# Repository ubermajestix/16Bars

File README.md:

# 16Bars

16Bars is a utility module designed to display how many 
measures have elapsed on a seven segment display given a clock pulse. 
The module resets every 8 or 16 measures (bars) or when the reset button is pressed.

This is my first module design and I've made several simplifying design choices:
1. A 1U version would be much more convienient
2. Reset jack would be nice to play better with midi or modules that output reset
3. Midi support? Accept MIDI TRS input for start, stop, and reset?
4. LFO output with LFO reset, could use 1st bar, n/2 bars, and last bar to self patch musical phrased LFO
## Rev 3.2 Updates and Issues

## Rev 2.0 Updates and Issues
I was successfully able to get JLCPCB to manufacture and place a lot of SMD components as I don't have the time or gear to get into surface mount, win! 

I also breadboarded out and build test PCBS to validate significant portion of the Rev 2.0 design:
- Reset button uses a transistor to send a reset signal instead of directly sending +12v when pressed
- Two transistors to normalize a wide variety of incoming clock signal voltages and send +12v pulses to trigger the three counter ICs and blink the led in the reset button 
- 8 bar reset logic confirmed, 16 bar reset logic didn't work because I was rushing to get Rev 2.0 board to production.
- Built a switch test PCB. I ordered 4 different switches and after getting incorrect footprints for the seven segment leds from Mouser I didn't trust the switch footprints. I also wanted to validate the switch weight, height, footprint size tradeoffs, validate the switches are in-fact on-on SPDT, and ensure the switches are too able to be flipped by accident when patching as they control the reset logic and time signature (4/4 and 8/4). 

Issues
- The [surface mount transistors](https://www.lcsc.com/product-detail/Bipolar-Transistors-BJT_Jiangsu-Changjing-Electronics-Technology-Co-Ltd-C9634_C9634.html) do not work as intended. I am considering replacing them with through-hole NPN's I'm using on the breadboard to validate it's either a component problem or PCB routing problem. 

# Panel Design
Panel design ideas, PCB, and logo are in Panel/. I'm aiming for a wind theme throughout the design and naming.

Rev 2.0 panel design is coming along:

# LED Sheild Practice aka Clock Blink
The design and fabrication process can be intimidating for a beginner. What I've learned from
software development is to start easy and get something small all the way to production before tackling bigger
projects. 

I followed [Contextual Electronic's _Getting To Blinky 5.0](https://www.youtube.com/watch?v=BVhWh3AsXQs)_ to learn
KiCAD schematic design, PCB layout and design, and fabrication on a simple circuit.

I wanted to use a keyed power header, know it worked by lighting up an LED, and take a clock pulse in through a jack to light up an led.

I fabricated the boards and got the power led to light up from my Eurorack case! The blinking feature isn't working and
I'm debugging it as of March 2022. 

# Practice Panel
I also wanted to practice making a panel. Again, to simplify, I wanted to get the mounting holes placed correctly with oval
holes like Intellijel 1U modules b/c my rails are never exactly aligned top to bottom. I was planning to make a control panel for the
the ClockBlink board but I figured why not make a blank 1U panel with some Fiverr artwork? 

The blank panels turned out great, I fabbed them with OshPark.com in purple (their default) and black (After Dark). The holes
line up and they were $7 and $12 shipped for three copies.

# License
[Attribution 4.0 International (CC BY 4.0)](https://creativecommons.org/licenses/by/4.0/)

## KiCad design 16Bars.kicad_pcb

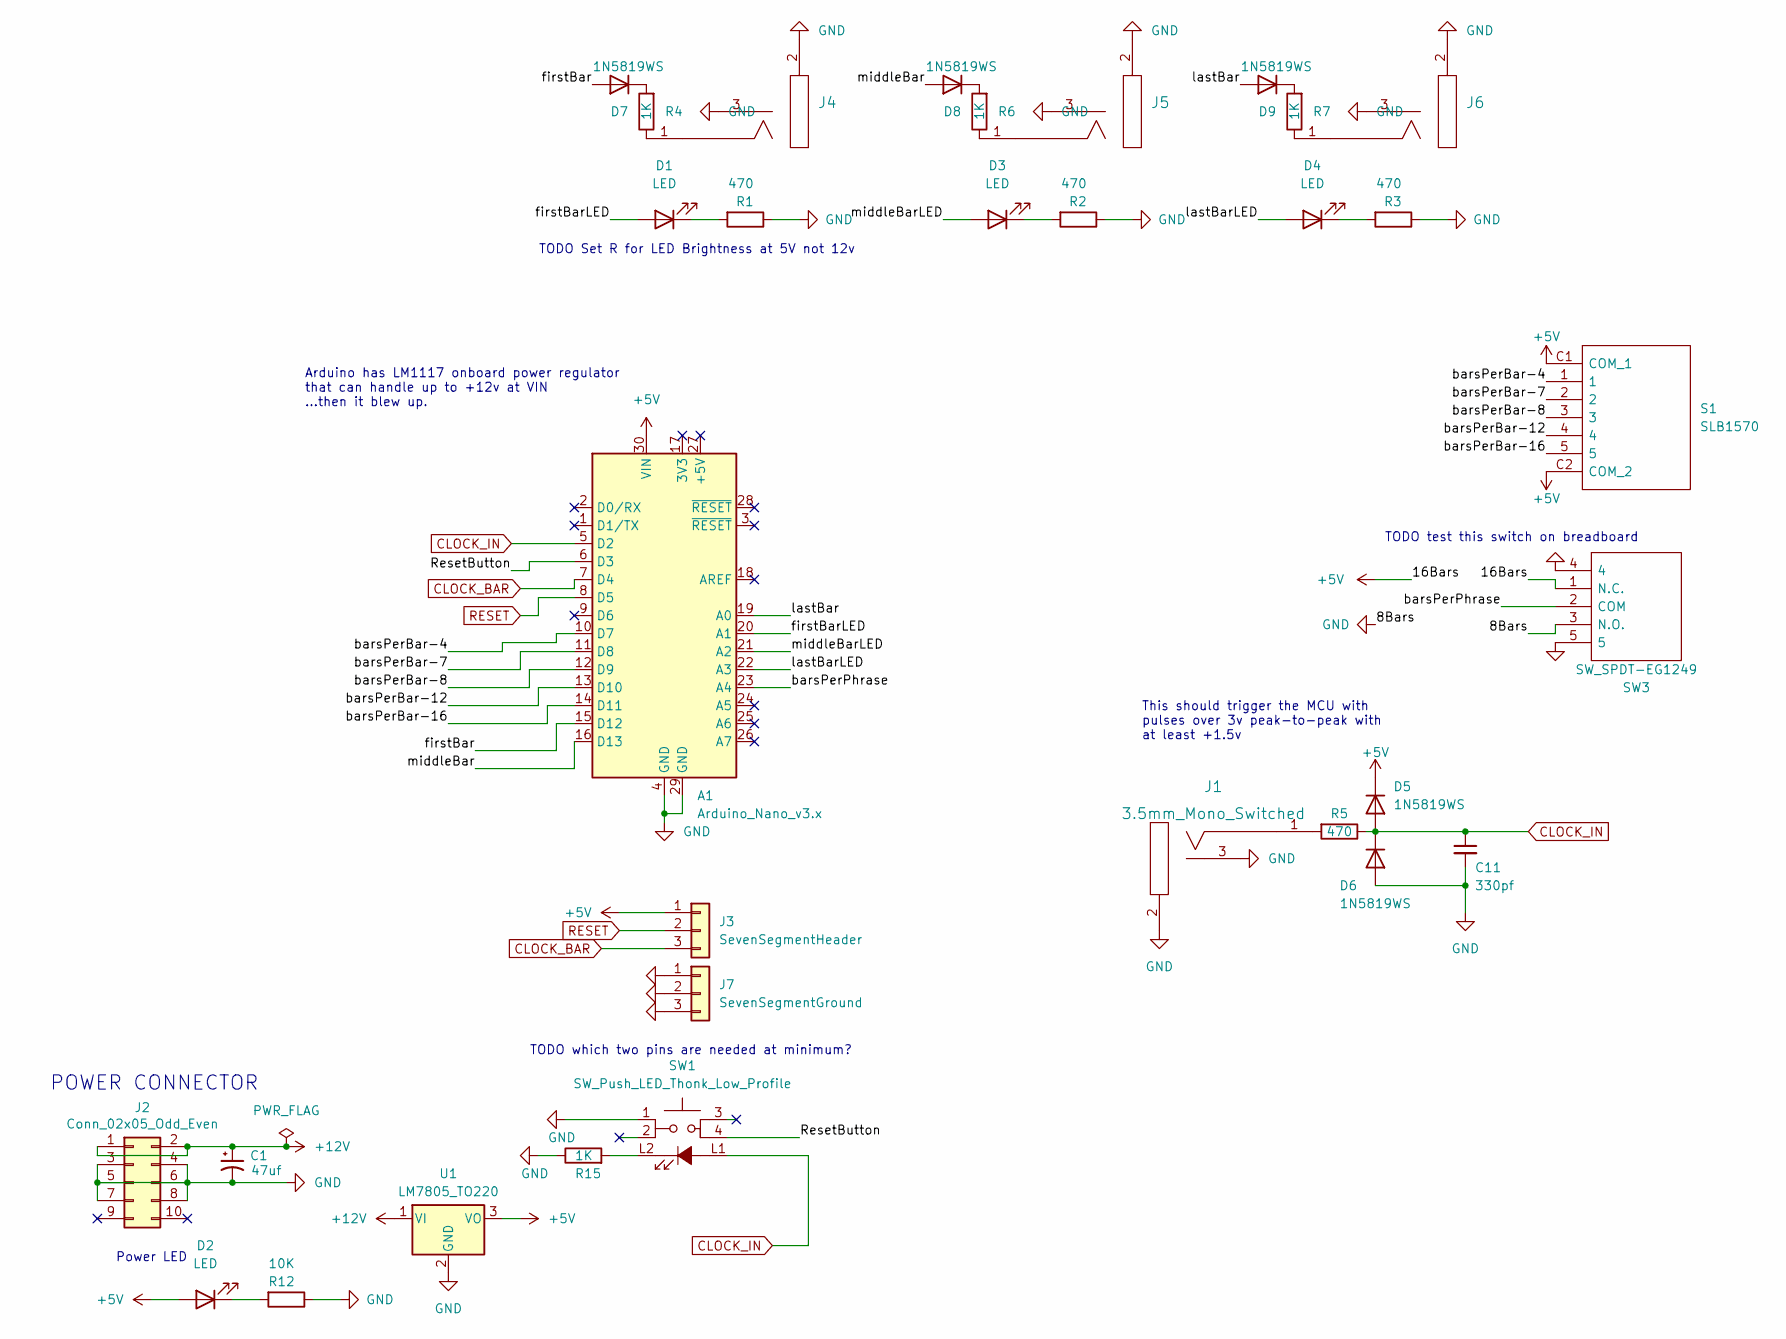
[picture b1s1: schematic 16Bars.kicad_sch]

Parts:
A1: Arduino_Nano_v3.x; Arduino_Nano
C1: 47uf; CP_Radial_D5.0mm_P2.00mm
C11: 330pf; C_0402_1005Metric; Manufacturer_Part_Number C13533; LCSC C13533
D1, D3, D4: LED; LED_D3.0mm
D2: LED; LED_0603_1608Metric; Manufacturer_Part_Number C2290; LCSC C2290
D5, D6, D7, D8, D9: 1N5819WS; D_SOD-323; Manufacturer_Part_Number C191023; LCSC C191023
J1, J4, J5, J6: 3.5mm_Mono_Switched; EighthInch_PJ398SM; Part Number WQP-WQP518MA
J2: Conn_02x05_Odd_Even; PinHeader_2x05_P2.54mm_Vertical
J3: SevenSegmentHeader; Pins_1x03_2.54mm_TH_AudioInsRGndL; Part Number 1-0301FBV0T
J7: SevenSegmentGround; Pins_1x03_2.54mm_TH_AudioInsRGndL; Part Number 1-0301FBV0T
R1, R2, R3: 470; R_0402_1005Metric; Manufacturer_Part_Number C4109; LCSC C25117
R4, R6, R7, R15: 1K; R_0402_1005Metric; Manufacturer_Part_Number C4109; LCSC C4410
R5: 470; R_0402_1005Metric; Manufacturer_Part_Number C25792; LCSC C25117
R12: 10K; R_0402_1005Metric; Manufacturer_Part_Number C4109; LCSC C4109
S1: SLB1570; Mouser Part Number 642-SLB1570
SW1: SW_Push_LED_Thonk_Low_Profile; ThonkLowProfileButton
SW3: SW_SPDT-EG1249; EG1249; Mouser Part Number 612-EG1249
U1: LM7805_TO220; TO-220-3_Vertical

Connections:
+5V: A1.30 (VIN), D2.2 (A), D5.1 (K), J3.1, S1.C1 (COM_1), S1.C2 (COM_2), SW3.1 (N.C.), U1.3 (VO)
+12V: C1.1, J2.1, J2.2, U1.1 (VI)
/ResetButton: A1.6 (D3), SW1.4
/barsPerBar-4: A1.10 (D7), S1.1
/barsPerBar-7: A1.11 (D8), S1.2
/barsPerBar-8: A1.12 (D9), S1.3
/barsPerBar-12: A1.13 (D10), S1.4
/barsPerBar-16: A1.14 (D11), S1.5
/barsPerPhrase: A1.23 (A4), SW3.2 (COM)
/firstBar: A1.15 (D12), D7.2 (A)
/firstBarLED: A1.20 (A1), D1.2 (A)
/lastBar: A1.19 (A0), D9.2 (A)
/lastBarLED: A1.22 (A3), D4.2 (A)
/middleBar: A1.16 (D13), D8.2 (A)
/middleBarLED: A1.21 (A2), D3.2 (A)
CLOCK_BAR: A1.7 (D4), J3.3
CLOCK_IN: A1.5 (D2), C11.1, D5.2 (A), D6.1 (K), R5.1, SW1.L1
GND: A1.4 (GND), A1.29 (GND), C1.2, C11.2, D6.2 (A), J1.2 (SHEILD), J1.3 (SW), J2.3, J2.4, J2.5, J2.6, J2.7, J2.8, J4.2 (SHEILD), J4.3 (SW), J5.2 (SHEILD), J5.3 (SW), J6.2 (SHEILD), J6.3 (SW), J7.1, J7.2, J7.3, R1.1, R2.1, R3.1, R12.1, R15.1, SW1.1, SW3.3 (N.O.), SW3.4, SW3.5, U1.2 (GND)
unnamed: D1.1 (K), R1.2
unnamed: D2.1 (K), R12.2
unnamed: D3.1 (K), R2.2
unnamed: D4.1 (K), R3.2
unnamed: D7.1 (K), R4.2
unnamed: D8.1 (K), R6.2
unnamed: D9.1 (K), R7.2
unnamed: J1.1 (SIG), R5.2
unnamed: J4.1 (SIG), R4.1
unnamed: J5.1 (SIG), R6.1
unnamed: J6.1 (SIG), R7.1
unnamed: R15.2, SW1.L2
RESET: A1.8 (D5), J3.2

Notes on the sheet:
POWER CONNECTOR
Arduino has LM1117 onboard power regulator that can handle up to +12v at VIN ...then it blew up.
Power LED
TODO test this switch on breadboard
TODO which two pins are needed at minimum?
TODO Set R for LED Brightness at 5V not 12v
This should trigger the MCU with pulses over 3v peak-to-peak with at least +1.5v

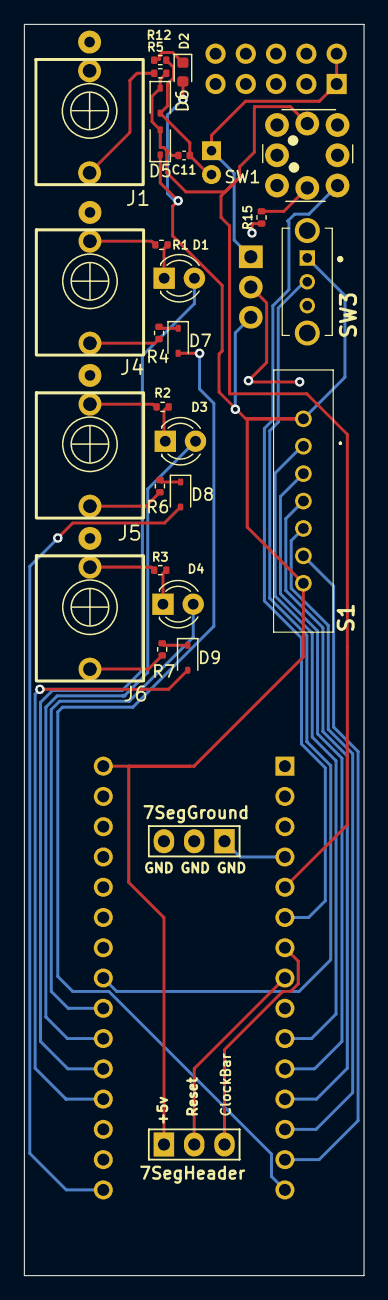
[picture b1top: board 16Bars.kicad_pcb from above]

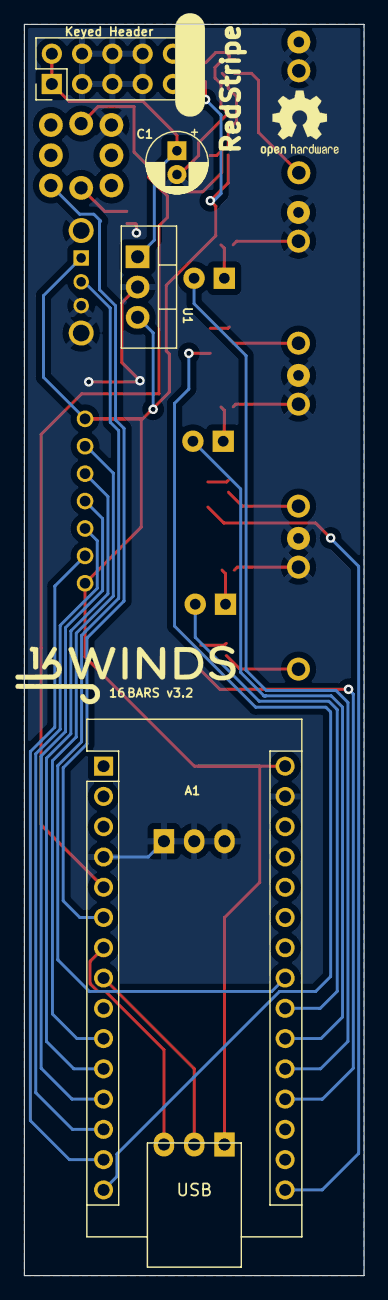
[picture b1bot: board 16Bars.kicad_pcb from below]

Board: 2 copper layers, 28.5 x 105.0 mm, 33 parts (5 on the bottom side), 31 nets.

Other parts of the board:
Ref**: Val**; 16WindsLogoJuly2023-12mm

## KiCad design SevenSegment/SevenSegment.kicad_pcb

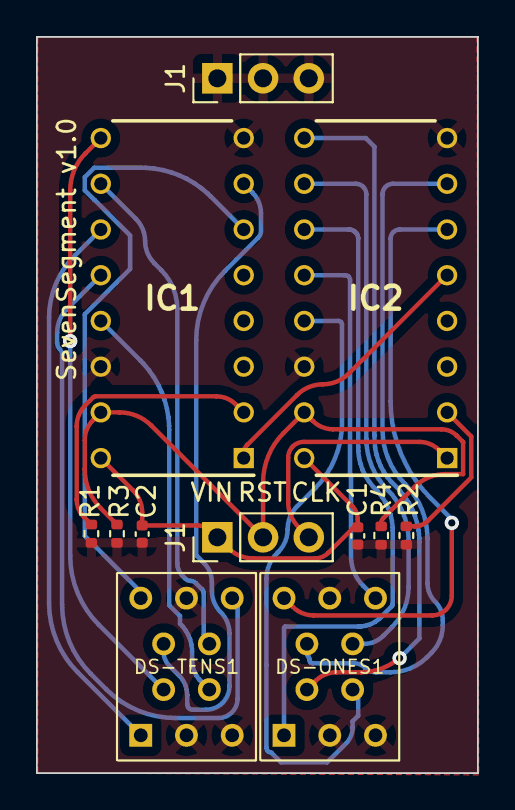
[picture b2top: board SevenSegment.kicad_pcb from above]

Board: 2 copper layers, 24.5 x 40.9 mm, 12 parts (0 on the bottom side), 21 nets.

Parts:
C1, C2: 100nf; C_0402_1005Metric
DS-ONES1: TDSR0760
DS-TENS1: TDSR0760
IC1, IC2: CD4033BE; DIP794W53P254L1930H508Q16N
J1, J1#2: Conn_01x04; PinHeader_1x03_P2.54mm_Vertical
R1, R2, R3, R4: 10K; R_0402_1005Metric

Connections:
+12V: C1.2, C2.2, IC1.16 (VDD), IC2.16 (VDD), J1.1
/A1: DS-ONES1.7 (A), IC2.10 (A)
/A2: DS-TENS1.7 (A), IC1.10 (A)
/B1: DS-ONES1.6 (B), IC2.12 (B)
/B2: DS-TENS1.6 (B), IC1.12 (B)
/C1: DS-ONES1.4 (C), IC2.13 (C)
/C2: DS-TENS1.4 (C), IC1.13 (C)
/D1: DS-ONES1.2 (D), IC2.9 (D)
/D2: DS-TENS1.2 (D), IC1.9 (D)
/E1: DS-ONES1.1 (E), IC2.11 (E)
/E2: DS-TENS1.1 (E), IC1.11 (E)
/F1: DS-ONES1.10 (F), IC2.6 (F)
/F2: DS-TENS1.10 (F), IC1.6 (F)
/G1: DS-ONES1.9 (G), IC2.7 (G)
/G2: DS-TENS1.9 (G), IC1.7 (G)
/RESET: IC1.15 (RESET), IC2.15 (RESET), J1.2, R3.2, R4.2
CARRY_1: IC1.1 (CLOCK), IC2.5 (CARRYOUT)
CLOCK_BAR: IC2.1 (CLOCK), J1.3
GND: C1.1, C2.1, DS-ONES1.3 (A(C)_1), DS-ONES1.5 (DP), DS-ONES1.8 (A(C)_2), DS-TENS1.3 (A(C)_1), DS-TENS1.5 (DP), DS-TENS1.8 (A(C)_2), IC1.8 (VSS), IC1.14 (LAMPTEST), IC2.8 (VSS), IC2.14 (LAMPTEST), J1#2.1, J1#2.2, J1#2.3, R1.2, R2.2, R3.1, R4.1
unnamed: IC1.2 (CLOCKINHIBIT), R1.1
unnamed: IC2.2 (CLOCKINHIBIT), R2.1

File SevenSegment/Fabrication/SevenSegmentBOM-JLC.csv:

Id,Designator,Footprint,Comment,LCSC Part Number
3,"R4,R3,R2,R1",R_0402_1005Metric,10K,C25744
5,"C2,C1",C_0402_1005Metric,100nf,C1525

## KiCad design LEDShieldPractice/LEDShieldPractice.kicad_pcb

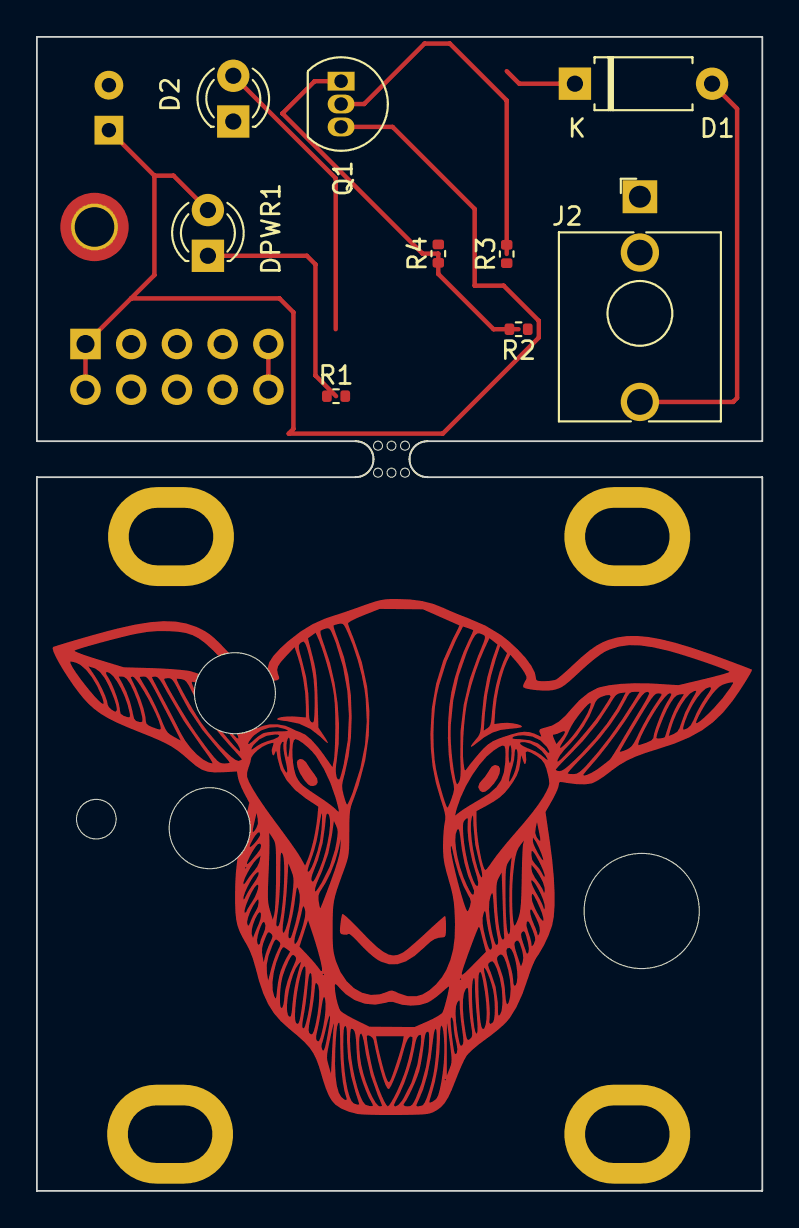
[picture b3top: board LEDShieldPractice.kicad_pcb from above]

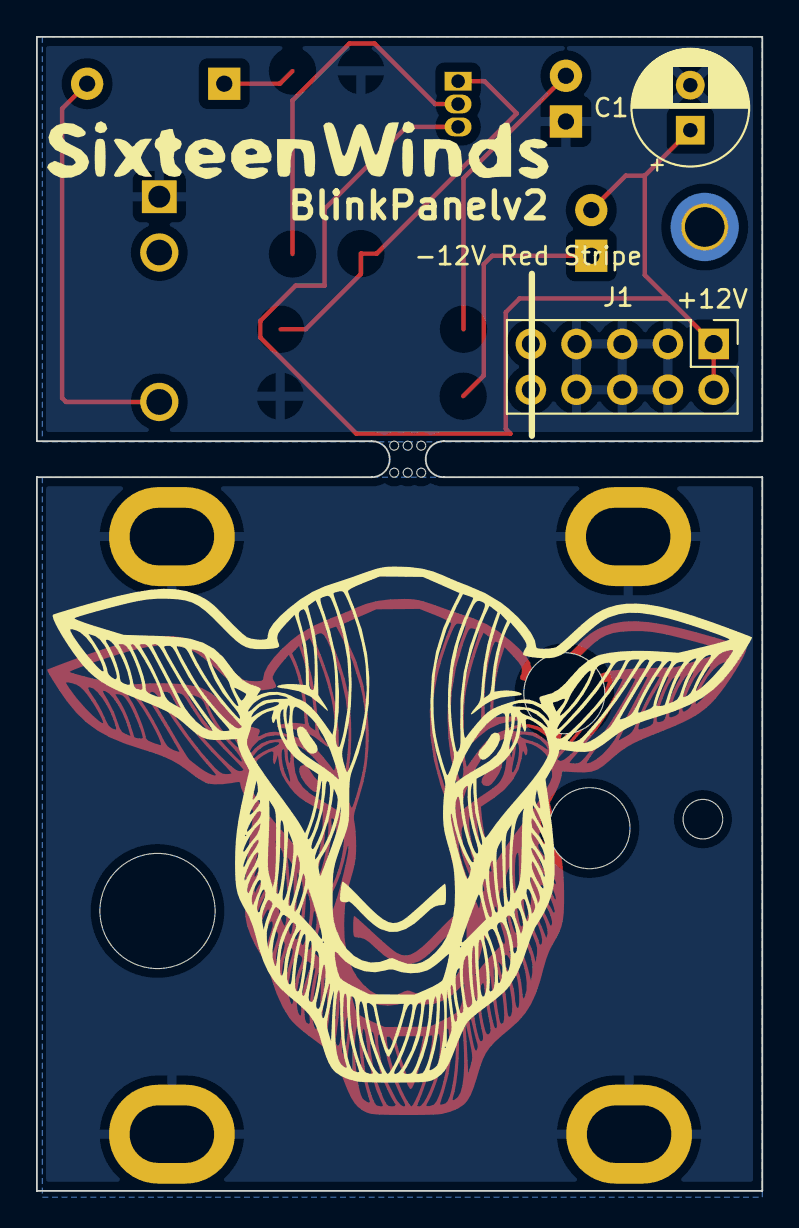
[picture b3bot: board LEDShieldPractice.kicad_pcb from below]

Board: 2 copper layers, 40.3 x 64.1 mm, 16 parts (2 on the bottom side), 9 nets.

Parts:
C1: 47uf; CP_Radial_D6.3mm_P2.50mm
D1: 1N4148; D_A-405_P7.62mm_Horizontal
D2: LED; LED_D3.0mm
DPWR1: LED; LED_D3.0mm
H1, H2, H3, H4: MountingHole_Pad; MountingHole_3.2mm_M3_IntellijelOval_Pad
J1: Conn_02x05_Odd_Even; PinHeader_2x05_P2.54mm_Vertical
J2: CLOCK_IN; Jack_3.5mm_QingPu_WQP-PJ398SM_Vertical_CircularHoles
Q1: 2N3904; TO-92_Inline
R1, R2: 2000; R_0402_1005Metric
R3: 47K; R_0402_1005Metric
R4: 10k; R_0402_1005Metric
mouse-bite-2mm-slot: VAL**; mouse-bite-2mm-slot

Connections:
+12V: C1.1, DPWR1.2 (A), J1.1, J1.2, Q1.3 (C)
-12V: J1.9, J1.10
CLOCK: Q1.1 (E), R2.1, R4.1
GND: C1.2, D2.1 (K), H1.1, H2.1, H3.1, H4.1, J1.3, J1.4, J1.5, J1.6, J1.7, J1.8, J2.S, R1.2, R4.2
unnamed: D1.1 (K), R3.2
unnamed: D1.2 (A), J2.T
unnamed: D2.2 (A), R2.2
unnamed: DPWR1.1 (K), R1.1
unnamed: Q1.2 (B), R3.1

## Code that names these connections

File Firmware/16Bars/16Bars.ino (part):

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  firstBar = LOW;
  middleBar = LOW;
  lastBar = LOW;
  digitalWrite(firstBarOutPin, firstBar);
  digitalWrite(firstBarLEDPin, firstBar);
  digitalWrite(middleBarOutPin, middleBar);
  digitalWrite(middleBarLEDPin, middleBar);
  digitalWrite(lastBarOutPin, lastBar);
  digitalWrite(lastBarLEDPin, lastBar);
  changeBeatsAndBars();
  // Reset 4033's to "00"
  resetOutPin.write(HIGH);
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    clockBarPin.write(HIGH);
    clockBarPin.write(LOW);
  }
  digitalWrite(firstBarOutPin, firstBar);
  digitalWrite(firstBarLEDPin, firstBar);
  digitalWrite(middleBarOutPin, middleBar);
  digitalWrite(middleBarLEDPin, middleBar);
  digitalWrite(lastBarOutPin, lastBar);
  digitalWrite(lastBarLEDPin, lastBar);

  
  // Reset output pins after writing any changes.
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  // length of the input clock pulse (~5 milliseconds).
  clockBarState = LOW;
  resetPhrase = LOW;
  firstBar = LOW; // TODO first bar and reseet are the same thing. Can we reset the 4033's, light up an led, and input to a schmitt trigger with one pin?
  middleBar = LOW;
  lastBar = LOW;
  
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// Changes to the barsPerPhrase and beatsPerBar switches will be picked up on the next phrase reset or when the reset button is pushed. 
void changeBeatsAndBars(){
  // Read phrase length, if HIGH set to 16 bars, if LOW set to 8 bars
  barsPerPhrase = digitalRead(barsPerPhrasePinNum) ? barsPerPhraseValues[1] : barsPerPhraseValues[0];
  debug("bars "); debug(barsPerPhrasePinNum); debug(" "); debug(digitalRead(barsPerPhrasePinNum)); debug(" "); debugln(barsPerPhrase);
  // Read 5 position switch to set beatsPerBar, 
  // each switch position is connected to it's own input pullup
  for (int i = 0; i < 5; i++) {
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
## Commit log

2022-02-14 Let there be bars
2022-02-17 LEDShield, Panel, Improve 16bars
2022-02-18 OshPark AfterDark Sheep Panel
2022-02-23 Finished schematic and footprints
2022-02-23 Rough PCB Layout
2022-02-23 Update PCB layout, shrunk silkscreen size
2022-02-24 Add Datasheets
2022-02-25 PCB Layout Complete
2022-02-25 Updated Gerbers after width change
2022-02-25 Update Gerber Zip
2022-02-28 Resize PCB
2022-03-01 Backup
2022-03-01 Resize ClockBlink PCB
2022-03-03 Add measurements to 1U Blank
2022-12-15 Update LED Shield Practice
    Updated footprints for flush fitting resistors and reran traces. Build 2nd board from last years run, changed led resistors from 500 to 2k, 500 burned out leds with 12v.
    Board works but the clock led is lit and turns off when it receives a signal, the transistor is acting as a logic NOT, unsure how to debug, need time on the breadboard.
2022-12-15 Fix Transitor Logic Add LED Button Datasheet
2022-12-19 Update LED Panel layout, added panel with mouse bites.
2022-12-20 Update gitignore
2022-12-21 Start moving components to surface mount
    Looking at Super16 project I think maybe I mounted my transistor incorrectly and that I should probably voltage divide the input to it significantly. OR I used a PNP instead of NPN transistor, need t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
2023-01-04 Surface Mount Resistors and Caps, fix 7segment footprint
2023-01-05 Tracks for 7Seg LEDs
2023-01-05 Fix transistor logic. TODO resistor values.
2023-01-05 Ignore auto_saved_files
2023-01-05 Update PCB and Schematic Footprints
    Better 7Seg layout
    Update 7seg footprint
2023-01-05 Add Thonk Low Profile LED Button Symbol
2023-01-05 Really Ignore Auto Saved Files
2023-01-05 Add PowerLED. Add ThonkButton Symbol and Footprint
2023-01-06 Complete Surface Mount Version
    Fix 16BarsReset Label by adding resistor
    Add TODOs for clock and bar division switches
2023-01-09 SMD Transistors and LED
    Move fabrication files to Fabrication dir
2023-01-09 Add LCSC Part Numbers
2023-01-09 LCSC Part Numbers
2023-01-11 Add 4MS Jack Symbol and Footprint
2023-01-13 Add Power Regulation
    Described in this talk by Paul Schreiber of Synthesis Technology https://youtu.be/cBGyEBQnIws
2023-01-24 Add component measurments from top left of board, start panel files.
2023-01-24 Panel Design Ideas
2023-01-25 Add Falstad POC Circuit
2023-01-28 Panel with artwork, holes, cutouts.
    Panel size was 8HP shrunk to 6HP.
    Logo is too big.
2023-01-28 Fix Logo. Generate Gerbers
2023-01-28 Fix cutout, remove copper beneath
    TODO add M3 hole
2023-01-28 Don't override measurement values, it only changes the text.
    User4 layer in yellow is correct. Only affected jack and button holes and they were only off by a few 100's of a mm, SHOULD be ok?
2023-01-29 Ground lamptest pin 14 on IC2
2023-01-30 Use schotky diodes on input remove transistor for led blink
    Model in Falstad, added transistor to correctly invert reset logic.
    TODO figure out reset button. Should reset 4510 and 4033's, 16bar-reset should only reset 4033's.
2023-01-31 [V2] Add Bar Counters and Switches
    Add switch for beats/bar
    Add switch for bars/phrase
    Add two 4510's for counting bars for configurable reset. Will support up to 128 bars/phrase, limited to 16 for now.
2023-02-01 Add diode on reset switch output
    Falstad model showed the reset button voltage flowing back to the output pin(s) of the bar counter and not triggering the reset pins. Adding a diode helped current flow.
2023-02-03 Updated Reset with Switch and 16 Bars
2023-02-04 Update Schematic From Falstad Model
    To reset the phrase two 4510's allow selecting phrase length of 4,8,16 bars.
    The clock divider 4510 now allows for 4/8 beats/bar.
2023-02-07 Add transistors to normalize the clock signal
2023-02-08 Normalize incoming clock, fix reset logic, logo
    Clock should now pickup very low voltage clocks. PGH Microvolt sends out 0.8v clock, not high enough to trigger CMOS logic.
    Flipped reset button so it's not connected directly to 12v with transistor. Use diode to OR button reset with PhraseReset clock signal.
    Mouser symbols need LibraryLoader installed from https://ms.componentsearchengine.com/pcb-libraries.php
2023-02-10 Update footprints
    Source switches from Mouser, possibly look into samples from E-Switch
2023-02-15 Change bars switch to SPDT
    Remove 4 bars option to make switch selection and footprint easier.
2023-02-15 Move project parts to Parts/
2023-02-15 Trying to organize footprints and symbols
    Trying to avoid having to use LibraryLoader to get symbols and footprints on all machines. Would love to have symbols and footprints local to the project. Looks like I have to migrate older SamacSys 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
2023-02-15 Use EG1249 switches in on-on config
    TODO: test on-on symbol configuration that I had to modify from the Mouser symbol/footprint.
2023-02-16 Update PCB with V2 changes
    F.Cu SMD assembly will provide much more room for tracks instead of routing around ICs on B.Cu.
2023-02-16 Seven Segment PCB Layout
2023-02-16 More PCB Layout
2023-02-16 Finish PCB Layout
2023-02-28 Fix DRC errors
2023-02-28 Add measurements for panel
2023-02-28 Update panel measurement font size
2023-02-28 Add logo to main board. Add readme for how to get images on pcb
2023-03-01 Rename README.txt to README.md
2023-03-02 Remove two mounting holes. Add full board measurements.
2023-03-02 Panel labels design
2023-03-04 Square 5.3mm panel cutouts for switch travel
    Cutout doesn't need to be the size of the switch body :laughing:
    Switch travel in datasheet is 2mm middle to middle with a 2mm wide switch so it should travel 4mm. Measuring switch confirms 4mm travel. Give 0.75mm margin all around
2023-03-06 Add testing points
2023-03-10 Add test points. Version layer test.
    Add test points on edge of pcb to test with alligator clips because that's what I have for my multimeter.
    The "16Bars Rev 2.0" I did in multiple layers to test look graphics in bare fr4 and bare copper
2023-03-10 Update panel design. Update logo on PCB
2023-03-11 Fabrication Output for Rev 2.0
2023-03-20 Remove PCB target in top left. Panel Design Updates
2023-03-22 Rev2.0 Resistor layout is incorrect.
2023-03-22 DC offset might be the issue
    CLOCK_IN is in an always on state, need to scope the incoming signal to find out for sure.
2023-03-22 Start Rev3
    Add first bar and last bar outputs to PCB, there should be room.
    Need to figure out output triggers and what's needed, Schmitt triggers?
2023-03-27 Debugging incoming clock issues.
2023-03-30 Add 16Bar reset AND logic transistor to schematic
2023-03-30 Add panel preview png
2023-03-30 Update README with 2.0 changes
2023-03-30 Revert to through hole resistors.
    Get resistor values correct for 16 bars reset AND gate.
    Add diode to Q2 reset button transistor.
    Fairly certain based on Falstad experiments JLCPCB placed PNP transistors instead of NPN, behavior of reset button in Falstad with PNP matches behavior observed on Rev2.0 PCB giving high reset signal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
2023-03-31 Track layout for TO-92 transistors. Needs DRC warning fixes.
2023-03-31 Rev 2.0 Build Photos
2023-03-31 More Rev 2.0 Build Photos
2023-03-31 Change size of build photo
2023-04-05 Cleanup fab layer, logo placement, and some routing
2023-04-19 Update reset button model to look like schematic
2023-05-02 Attempt to fix reset logic
    Falstad model helped get resistor values dialed in so we're sending >9v when 16 count is reached between the two 4510 counters and 12v is sent from the reset button. Removed diodes to increase voltag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
2023-05-11 Add level shifter Falstad model
2023-05-15 Add SevenSegment sub-board
2023-05-17 Layout SevenSegment Board. Nano Schematic
2023-05-18 Add 16Bars Firmware
2023-05-19 Rename file. Add Debounce lib.
2023-05-22 Get firmware working on different machine. Move files. Update logic.
2023-05-26 Add UberPin class.
    Class and header files must go in src/ or util/ for avr-gcc to find them
2023-05-30 Fix UberPin state. Getting reset logic closer.
2023-05-30 Figuring out reset button.
    Reset button release isn't getting picked up well so we're missing clock pulses.
2023-05-31 Add notes on how to modify changed method.
2023-05-31 Format files better, messing with changed method.
2023-05-31 Fixed reset logic.
    Reset now prevents clock from going through while held and keeps reset signal high.
2023-06-03 Add barsPerPhrasePin read on phrase reset.
    Redo bracket format.
2023-06-04 Add beatsPerBar pins.
2023-06-05 Add five position switch to choose beatsPerBar on reset.
2023-06-05 Add docs about when switch changes will be picked up.
2023-06-05 Add first, middle, and last bar logic.
2023-06-05 Fix first, middle, last, bar pin names.
2023-06-08 Add firmware todos.
2023-06-08 Add LED output pins. Hookup pins in schematic.
2023-06-08 Add LCSC power regulator. Add SLB1570 5 position switch.
2023-06-09 Add output jacks and leds.
2023-06-10 Verified 1P5T Switch on Breadboard.
2023-06-12 Remove AMS1117
    Arduino has one onboard!
2023-06-12 Add labels for beatsPerBar
2023-06-12 Set LED footprints
2023-06-12 Update PCB with Arduino. Add Miduino subproject.
2023-06-12 Miduino TODOs
2023-06-12 Reposition SevenSegment Header
    Still needs to move up 3.2mm to fit existing panel design.
    Might need to rebuild seven segment board. With current jack placement (kinda close to the Nano, we'll see how well it solders), we could put the 4033's back on the board but we'd need 2x7 pin header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
    Other option is to build a control board and a panel board. Panel board would house buttons, switches, leds, jacks, and seven segments. Control board would house Nano, 4033's, SMD's, Power and Cap. C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
    The other opti
2023-06-13 WIP Move Nano to bottom of board.
2023-06-13 Generate 3.0 Fabrication
    Added JLC bom python script.
2023-06-13 Add more fab files
    Resistors need to be updated on PCB
2023-06-13 Update PCB with resistor changes
2023-07-01 Fix PCB layout issues and pins not working on Nano.
2023-07-01 Update TODO.md
    After some research Boreas was not a very nice god of wind. Maybe we just use the latin names of winds instead. See Albrecht Durer's Armillary Sphere wind heads: https://www.helmink.com/antique-map/1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
2023-07-06 SevenSegment PCB v1.0
    Push TDSR0706's together, move header pins, add more header pins for mechanical stability, make board less wide, rounded tracks, moved ICs to top of board for better clearance.
2023-07-06 Fabrication Output v-1.0
2023-07-17 v3.1
2023-07-27 v3.1 Fabrication for PCB and Panel
2023-09-13 v3.2
2023-09-13 Add startup led flashing to firmware.
2023-09-14 Add output pin protection.
2024-05-14 Cleanup Comments. Add TODOs
    Finished the v3.2 build and it works! Noticed a few issues, zeros are not displaying probably from leaving the RBO and RBI (pins 3,4) on the 4033's floating, but need to test. I also left some commen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
2024-05-15 v3.2 Fabrication
2024-05-15 Update TODOs in SevenSegment
2024-05-15 Implement 01 to 16 counter
    Added internal clock testing mode.
2024-05-15 Increment to "01" on reset button press
2024-05-15 Add long press on reset at startup to enter test mode
2024-05-16 Simplify entering test mode. Add auto-reset after 4 seconds.
